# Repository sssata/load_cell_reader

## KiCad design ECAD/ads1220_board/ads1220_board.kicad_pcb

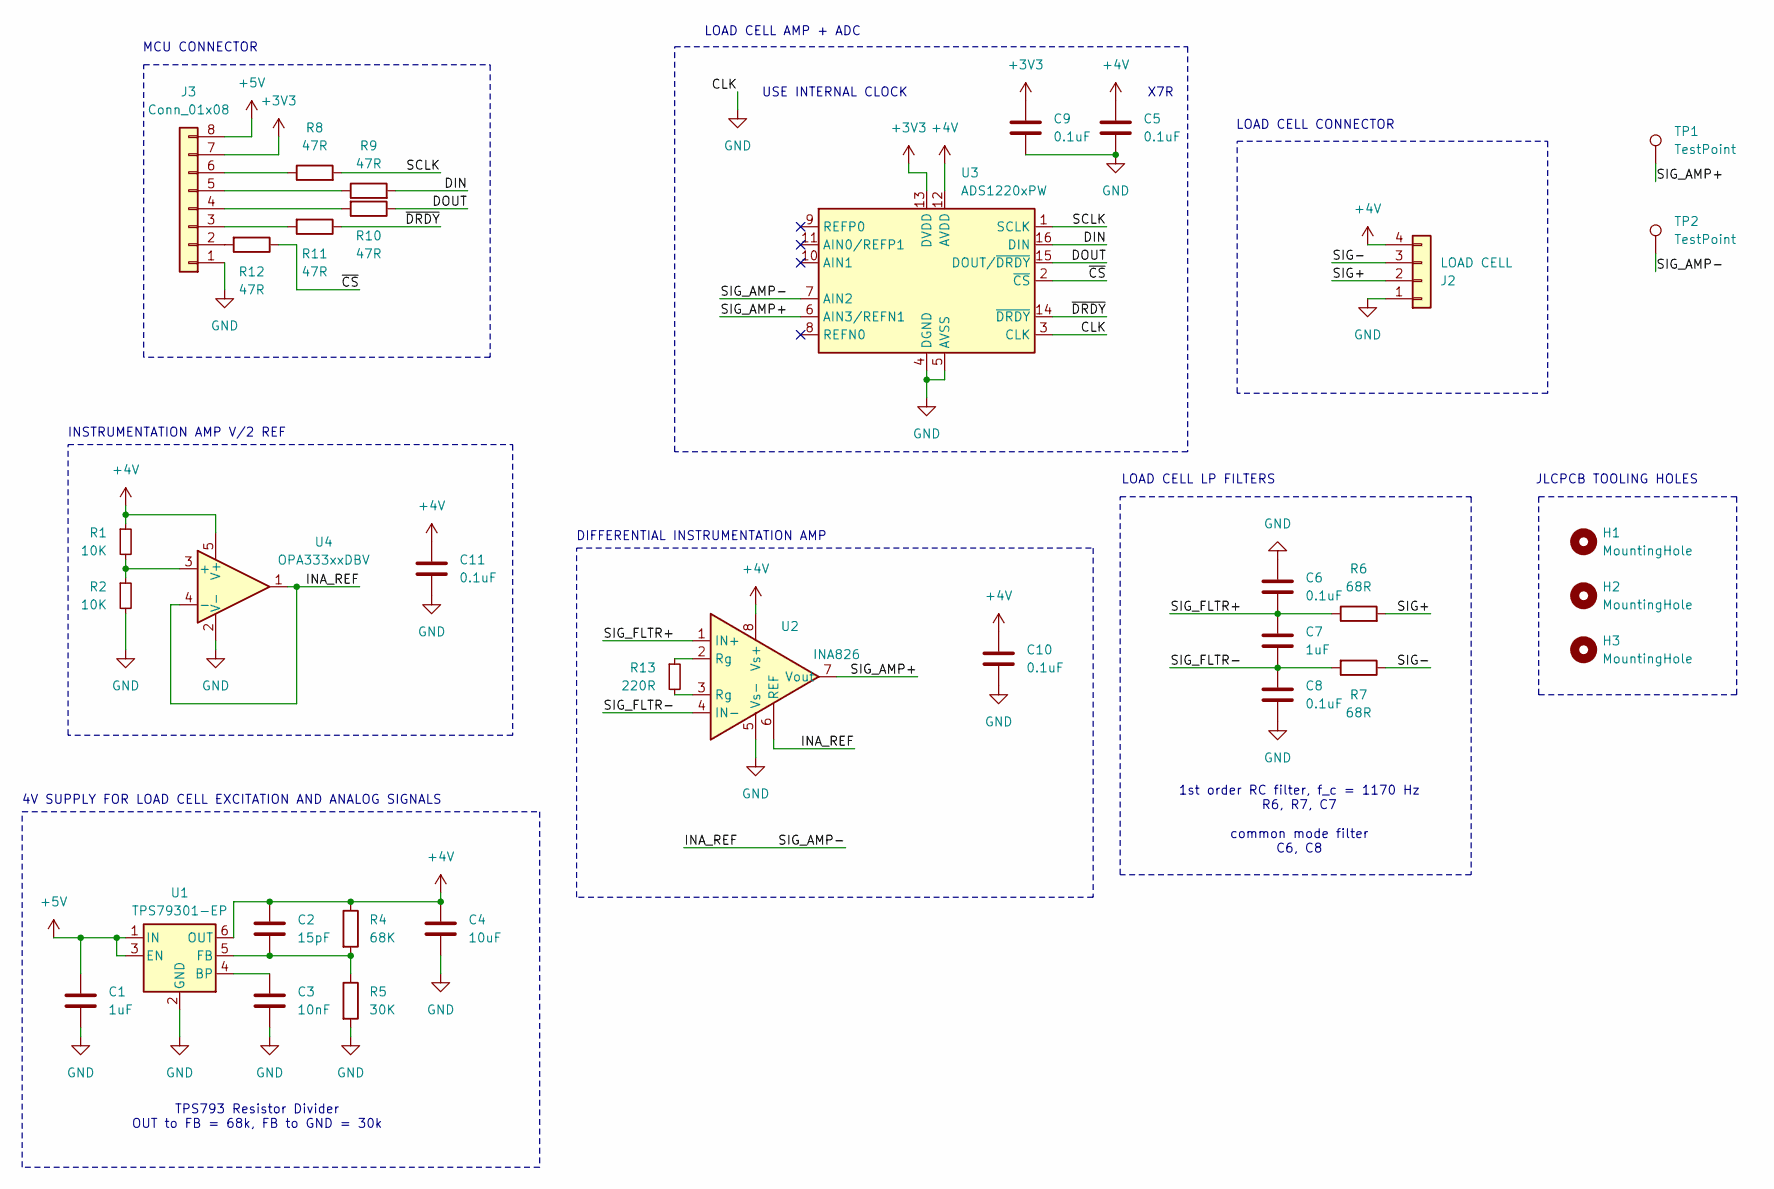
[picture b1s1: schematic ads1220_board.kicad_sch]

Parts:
C1, C7: 1uF; C_0402_1005Metric; JLC PN C52923
C2: 15pF; C_0402_1005Metric; JLC PN C1548
C3: 10nF; C_0402_1005Metric; JLC PN C15195
C4: 10uF; C_0603_1608Metric; JLC PN C19702
C5, C6, C8, C9, C10, C11: 0.1uF; C_0402_1005Metric; JLC PN C307331
H1, H2, H3: MountingHole; SMD Tooling Hole
J2: LOAD CELL; JST_PH_B4B-PH-K_1x04_P2.00mm_Vertical
J3: Conn_01x08; JST_PH_B8B-PH-K_1x08_P2.00mm_Vertical
R1, R2: 10K; R_0402_1005Metric; JLC PN C25744
R4: 68K; R_0603_1608Metric; JLC PN C23231
R5: 30K; R_0603_1608Metric; JLC PN C22984
R6, R7: 68R; R_0402_1005Metric; JLC PN C25131
R8, R9, R10, R11, R12: 47R; R_0603_1608Metric; JLC PN C23182
R13: 220R; R_0402_1005Metric; JLC PN C25091
TP1, TP2: TestPoint; TestPoint_Pad_1.0x1.0mm
U1: TPS79301-EP; SOT-23-6
U2: INA826; Texas_S-PDSO-G8_3x3mm_P0.65mm
U3: ADS1220xPW; TSSOP-16_4.4x5mm_P0.65mm
U4: OPA333xxDBV; SOT-23-5

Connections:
+3V3: C9.2, J3.7, U3.13 (DVDD)
+4V: C2.1, C4.1, C5.2, C10.2, C11.2, J2.4, R1.1, R4.1, U1.6 (OUT), U2.8 (Vs+), U3.12 (AVDD), U4.5 (V+)
+5V: C1.1, J3.8, U1.1 (IN), U1.3 (EN)
/DIN: R9.2, U3.16 (DIN)
/DOUT: R10.1, U3.15 (DOUT/~DRDY)
/INA_REF: TP2.1, U2.6 (REF), U3.7 (AIN2), U4.1, U4.4 (-)
/SCLK: R8.2, U3.1 (SCLK)
/SIG+: J2.2, R6.2
/SIG-: J2.3, R7.1
/SIG_AMP+: TP1.1, U2.7 (Vout), U3.6 (AIN3/REFN1)
/SIG_FLTR+: C6.2, C7.1, R6.1, U2.1 (IN+)
/SIG_FLTR-: C7.2, C8.1, R7.2, U2.4 (IN-)
/~CS: R12.1, U3.2 (~CS)
/~DRDY: R11.1, U3.14 (~DRDY)
GND: C1.2, C3.2, C4.2, C5.1, C6.1, C8.2, C9.1, C10.1, C11.1, J2.1, J3.1, R2.2, R5.2, U1.2 (GND), U2.5 (Vs-), U3.3 (CLK), U3.4 (DGND), U3.5 (AVSS), U4.2 (V-)
unnamed: J3.2, R12.2
unnamed: J3.3, R11.2
unnamed: J3.4, R10.2
unnamed: J3.5, R9.1
unnamed: J3.6, R8.1
unnamed: R13.1, U2.2 (Rg)
unnamed: R13.2, U2.3 (Rg)
unnamed: C3.1, U1.4 (BP)
unnamed: C2.2, R4.2, R5.1, U1.5 (FB)
unnamed: R1.2, R2.1, U4.3 (+)

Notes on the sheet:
X7R
INSTRUMENTATION AMP V/2 REF
JLCPCB TOOLING HOLES
LOAD CELL LP FILTERS
1st order RC filter, f_c = 1170 Hz R6, R7, C7 common mode filter C6, C8
LOAD CELL CONNECTOR
TPS793 Resistor Divider OUT to FB = 68k, FB to GND = 30k
MCU CONNECTOR
USE INTERNAL CLOCK
DIFFERENTIAL INSTRUMENTATION AMP
4V SUPPLY FOR LOAD CELL EXCITATION AND ANALOG SIGNALS
LOAD CELL AMP + ADC

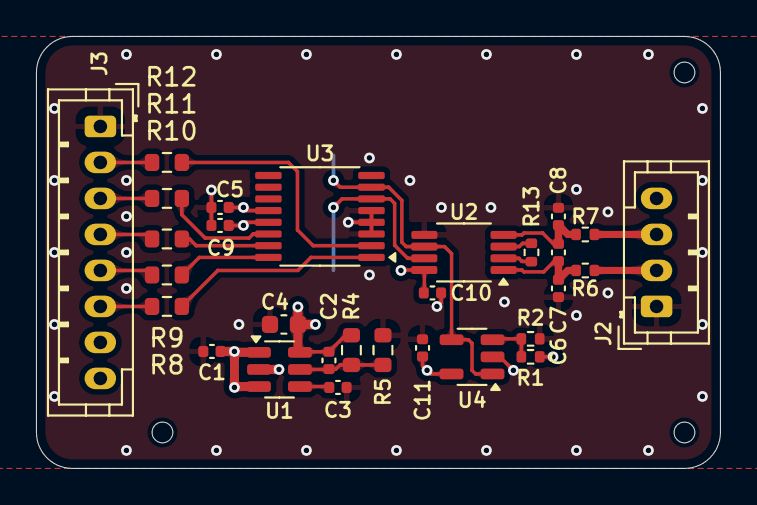
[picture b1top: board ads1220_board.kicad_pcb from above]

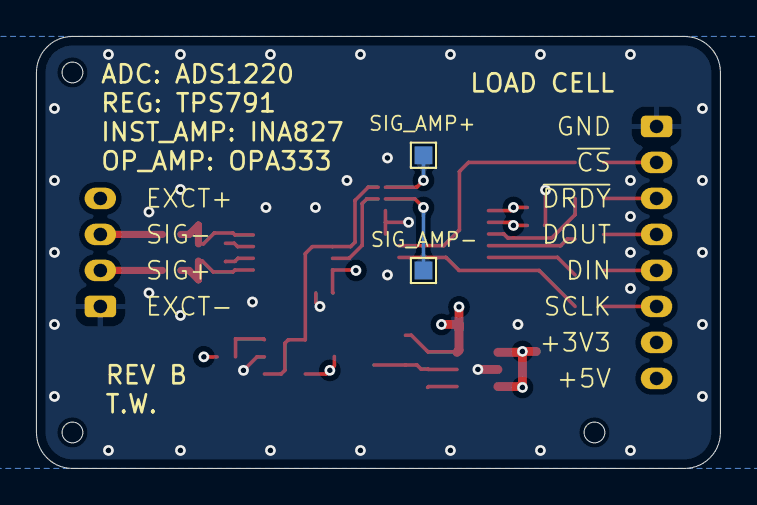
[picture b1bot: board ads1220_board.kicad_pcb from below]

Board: 4 copper layers, 38.0 x 24.0 mm, 34 parts (2 on the bottom side), 25 nets.

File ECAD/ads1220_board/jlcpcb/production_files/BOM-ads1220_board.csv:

Comment,Designator,Footprint,LCSC
10nF,C3,C_0402_1005Metric,C15195
15pF,C2,C_0402_1005Metric,C1548
10uF,C4,C_0603_1608Metric,C19702
30K,R5,R_0603_1608Metric,C22984
47R,"R10,R11,R12,R8,R9",R_0603_1608Metric,C23182
68K,R4,R_0603_1608Metric,C23231
220R,R13,R_0402_1005Metric,C25091
68R,"R6,R7",R_0402_1005Metric,C25131
10K,"R1,R2",R_0402_1005Metric,C25744
0.1uF,"C10,C11,C5,C6,C8,C9",C_0402_1005Metric,C307331
OPA333xxDBV,U4,SOT-23-5,C30878
TPS79301-EP,U1,SOT-23-6,C37151
ADS1220xPW,U3,TSSOP-16_4.4x5mm_P0.65mm,C48263
INA826,U2,Texas_S-PDSO-G8_3x3mm_P0.65mm,C51631
1uF,"C1,C7",C_0402_1005Metric,C52923
Conn_01x08,J3,JST_PH_B8B-PH-K_1x08_P2.00mm_Vertical,
LOAD CELL,J2,JST_PH_B4B-PH-K_1x04_P2.00mm_Vertical,
TestPoint,TP2,TestPoint_Pad_1.0x1.0mm,
TestPoint,TP1,TestPoint_Pad_1.0x1.0mm,

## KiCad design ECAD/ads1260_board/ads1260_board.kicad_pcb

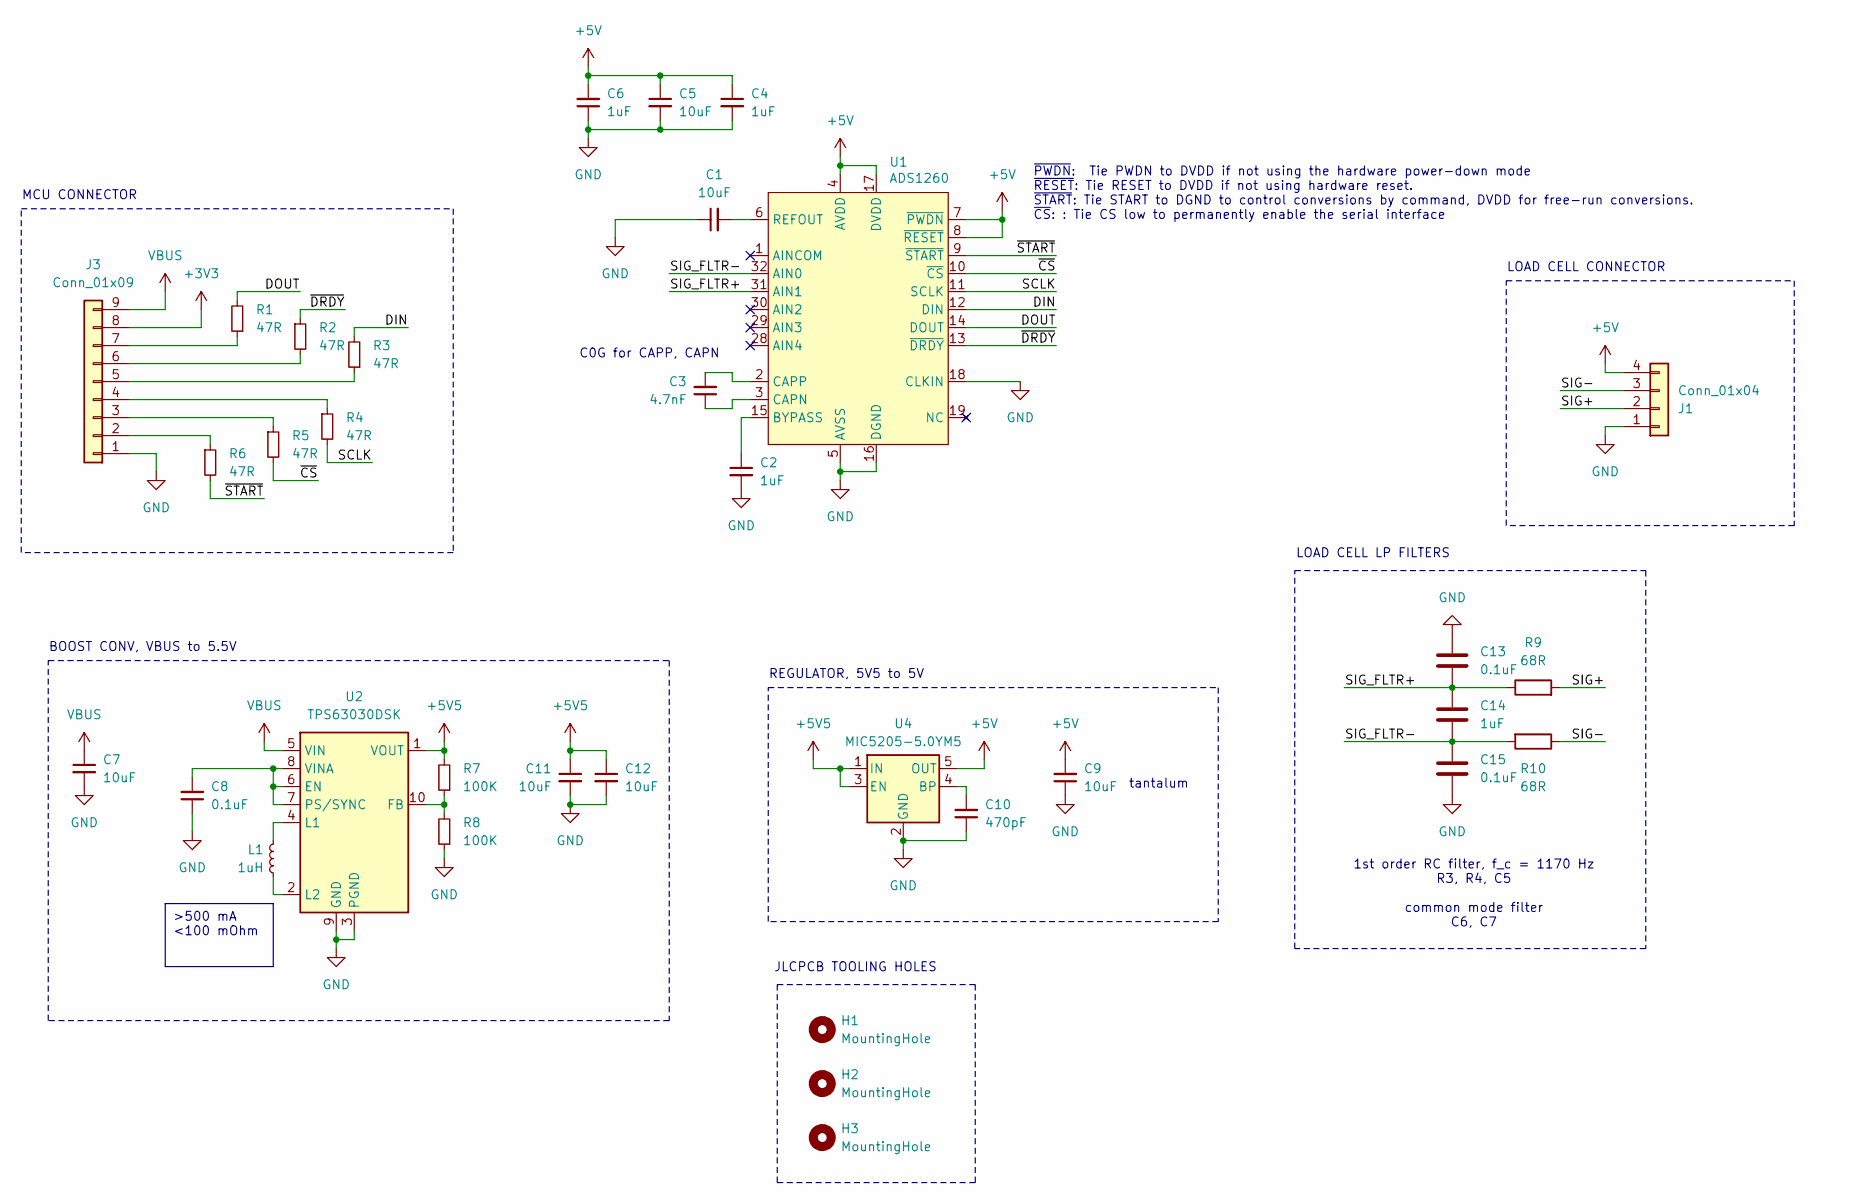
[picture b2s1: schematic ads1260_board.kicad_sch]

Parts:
C1, C5, C7, C9, C11, C12: 10uF; C_0603_1608Metric
C2, C4, C6, C14: 1uF; C_0402_1005Metric
C3: 4.7nF; C_0402_1005Metric
C8, C13, C15: 0.1uF; C_0402_1005Metric
C10: 470pF; C_0603_1608Metric
H1, H2, H3: MountingHole; SMD Tooling Hole
J1: Conn_01x04; JST_PH_B4B-PH-K_1x04_P2.00mm_Vertical
J3: Conn_01x09; JST_PH_B9B-PH-K_1x09_P2.00mm_Vertical
L1: 1uH; L_Murata_DFE201610P
R1, R2, R3, R4, R5, R6: 47R; R_0402_1005Metric
R7, R8: 100K; R_0402_1005Metric
R9, R10: 68R; R_0402_1005Metric
U1: ADS1260; VQFN-32-1EP_5x5mm_P0.5mm_EP3.15x3.15mm
U2: TPS63030DSK; WSON-10-1EP_2.5x2.5mm_P0.5mm_EP1.2x2mm
U4: MIC5205-5.0YM5; SOT-23-5

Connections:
+3V3: J3.8
+5V: C4.1, C5.1, C6.2, C9.2, J1.4, U1.4 (AVDD), U1.7 (~PWDN), U1.8 (~RESET), U1.17 (DVDD), U4.5 (OUT)
+5V5: C11.1, C12.1, R7.2, U2.1 (VOUT), U4.1 (IN), U4.3 (EN)
/DIN: R3.2, U1.12 (DIN)
/DOUT: R1.2, U1.14 (DOUT)
/SCLK: R4.2, U1.11 (SCLK)
/SIG+: J1.2, R9.2
/SIG-: J1.3, R10.1
/SIG_FLTR+: C13.2, C14.1, R9.1, U1.31 (AIN1)
/SIG_FLTR-: C14.2, C15.1, R10.2, U1.32 (AIN0)
/~CS: R5.2, U1.10 (~CS)
/~DRDY: R2.1, U1.13 (~DRDY)
/~START: R6.2, U1.9 (~START)
GND: C1.1, C2.2, C4.2, C5.2, C6.1, C7.2, C8.1, C9.1, C10.1, C11.2, C12.2, C13.1, C15.2, J1.1, J3.1, R8.1, U1.5 (AVSS), U1.16 (DGND), U1.18 (CLKIN), U1.33 (AVSS), U2.3 (PGND), U2.9 (GND), U2.11 (PGND), U4.2 (GND)
unnamed: J3.2, R6.1
unnamed: J3.3, R5.1
unnamed: J3.4, R4.1
unnamed: J3.5, R3.1
unnamed: J3.6, R2.2
unnamed: J3.7, R1.1
unnamed: C2.1, U1.15 (BYPASS)
unnamed: C3.1, U1.3 (CAPN)
unnamed: C3.2, U1.2 (CAPP)
unnamed: C1.2, U1.6 (REFOUT)
unnamed: C8.2, U2.6 (EN), U2.7 (PS/SYNC), U2.8 (VINA)
unnamed: R7.1, R8.2, U2.10 (FB)
unnamed: L1.2, U2.4 (L1)
unnamed: L1.1, U2.2 (L2)
unnamed: C10.2, U4.4 (BP)
VBUS: C7.1, J3.9, U2.5 (VIN)

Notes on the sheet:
>500 mA <100 mOhm
tantalum
REGULATOR, 5V5 to 5V
~{PWDN}: Tie PWDN to DVDD if not using the hardware power-down mode ~{RESET}: Tie RESET to DVDD if not using hardware reset. ~{START}: Tie START to DGND to control conversions by command, DVDD for free-run conversions. ~{CS}: : Tie CS low to permanently enable the serial interface
BOOST CONV, VBUS to 5.5V
MCU CONNECTOR
LOAD CELL LP FILTERS
1st order RC filter, f_c = 1170 Hz R3, R4, C5 common mode filter C6, C7
JLCPCB TOOLING HOLES
LOAD CELL CONNECTOR
C0G for CAPP, CAPN

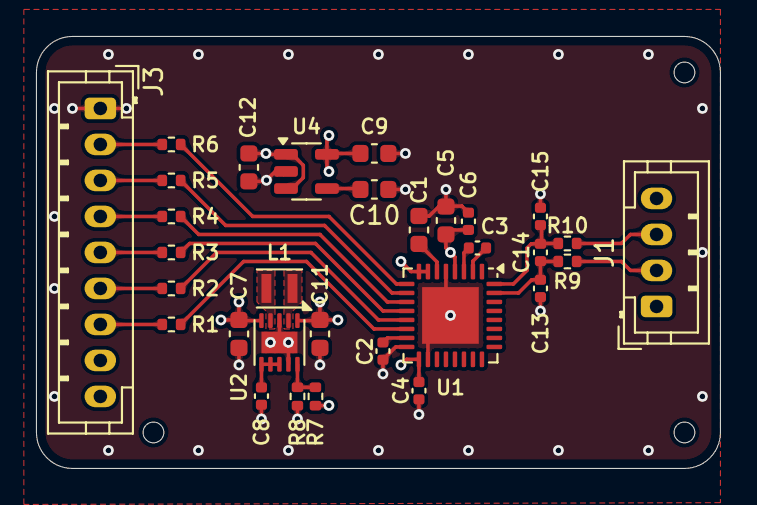
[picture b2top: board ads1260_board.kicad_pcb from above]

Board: 4 copper layers, 38.0 x 24.0 mm, 34 parts (0 on the bottom side), 29 nets.

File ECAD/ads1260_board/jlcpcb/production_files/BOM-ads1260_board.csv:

Comment,Designator,Footprint,LCSC
4.7nF,C3,C_0402_1005Metric,C1518204
1uH,L1,L_Murata_DFE201610P,C161082
470pF,C10,C_0603_1608Metric,C1620
47R,"R1,R10,R2,R3,R4,R5,R6,R9",R_0402_1005Metric,C25118
100K,"R7,R8",R_0402_1005Metric,C25741
0.1uF,"C13,C15,C8",C_0402_1005Metric,C307331
1uF,"C14,C2,C4,C6",C_0402_1005Metric,C52923
10uF,"C1,C11,C12,C5,C7,C9",C_0603_1608Metric,C96446

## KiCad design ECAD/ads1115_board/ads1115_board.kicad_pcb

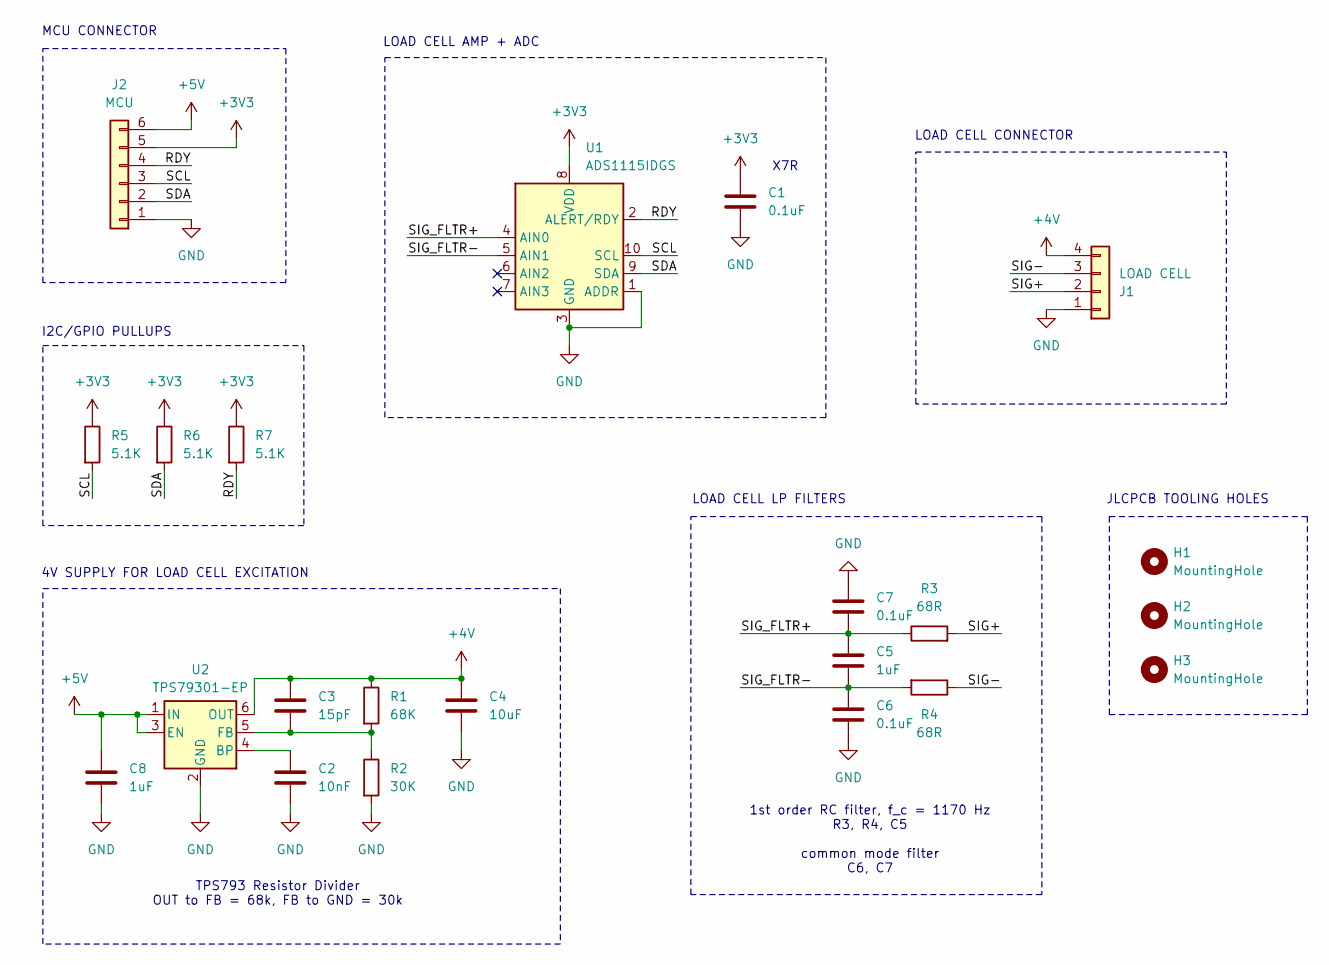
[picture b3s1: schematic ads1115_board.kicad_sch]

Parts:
C1, C6, C7: 0.1uF; C_0402_1005Metric
C2: 10nF; C_0402_1005Metric
C3: 15pF; C_0402_1005Metric
C4: 10uF; C_0603_1608Metric
C5, C8: 1uF; C_0402_1005Metric
H1, H2, H3: MountingHole; SMD Tooling Hole
J1: LOAD CELL; JST_PH_B4B-PH-K_1x04_P2.00mm_Vertical
J2: MCU; JST_PH_B6B-PH-K_1x06_P2.00mm_Vertical
R1: 68K; R_0402_1005Metric
R2: 30K; R_0402_1005Metric
R3, R4: 68R; R_0402_1005Metric
R5, R6, R7: 5.1K; R_0402_1005Metric
U1: ADS1115IDGS; TSSOP-10_3x3mm_P0.5mm
U2: TPS79301-EP; SOT-23-6

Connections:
+3V3: C1.2, J2.5, R5.1, R6.1, R7.1, U1.8 (VDD)
+4V: C3.1, C4.1, J1.4, R1.1, U2.6 (OUT)
+5V: C8.1, J2.6, U2.1 (IN), U2.3 (EN)
/RDY: J2.4, R7.2, U1.2 (ALERT/RDY)
/SCL: J2.3, R5.2, U1.10 (SCL)
/SDA: J2.2, R6.2, U1.9 (SDA)
/SIG+: J1.2, R3.2
/SIG-: J1.3, R4.1
/SIG_FLTR+: C5.1, C7.2, R3.1, U1.4 (AIN0)
/SIG_FLTR-: C5.2, C6.1, R4.2, U1.5 (AIN1)
GND: C1.1, C2.2, C4.2, C6.2, C7.1, C8.2, J1.1, J2.1, R2.2, U1.1 (ADDR), U1.3 (GND), U2.2 (GND)
unnamed: C2.1, U2.4 (BP)
unnamed: C3.2, R1.2, R2.1, U2.5 (FB)

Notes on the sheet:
LOAD CELL AMP + ADC
MCU CONNECTOR
1st order RC filter, f_c = 1170 Hz R3, R4, C5 common mode filter C6, C7
JLCPCB TOOLING HOLES
LOAD CELL CONNECTOR
TPS793 Resistor Divider OUT to FB = 68k, FB to GND = 30k
I2C/GPIO PULLUPS
LOAD CELL LP FILTERS
X7R
4V SUPPLY FOR LOAD CELL EXCITATION

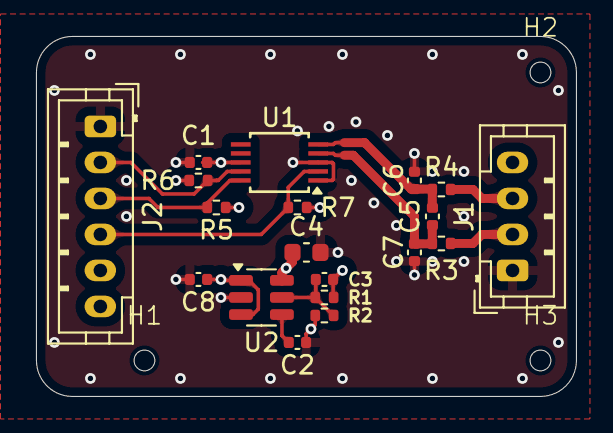
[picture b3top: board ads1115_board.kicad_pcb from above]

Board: 4 copper layers, 30.0 x 20.0 mm, 22 parts (0 on the bottom side), 13 nets.

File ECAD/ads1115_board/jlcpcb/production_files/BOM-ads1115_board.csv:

Comment,Designator,Footprint,LCSC
10nF,C2,C_0402_1005Metric,C15195
0.1uF,"C1,C6,C7",C_0402_1005Metric,C1525
15pF,C3,C_0402_1005Metric,C1548
68R,"R3,R4",R_0402_1005Metric,C25131
30K,R2,R_0402_1005Metric,C25776
5.1K,"R5,R6,R7",R_0402_1005Metric,C25905
68K,R1,R_0402_1005Metric,C36871
1uF,"C5,C8",C_0402_1005Metric,C52923
10uF,C4,C_0603_1608Metric,C96446
LOAD CELL,J1,JST_PH_B4B-PH-K_1x04_P2.00mm_Vertical,
MCU,J2,JST_PH_B6B-PH-K_1x06_P2.00mm_Vertical,
TPS79301-EP,U2,SOT-23-6,
ADS1115IDGS,U1,TSSOP-10_3x3mm_P0.5mm,

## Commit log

2024-05-07 various changes
2024-05-12 add iir filter
2024-07-08 update ads1220 schematic
2024-07-15 change from 2 ina to 1
2024-07-15 add ads1220 driver
2024-11-20 update, add second sensor
2024-11-26 Move adc reading to second core
